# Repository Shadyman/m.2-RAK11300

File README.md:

# RAK11300 LoRa Module on m.2 Key A-E

This is a board in the _m.2 Key A-E_ form factor to allow the use of the [RAK11300](https://docs.rakwireless.com/Product-Categories/WisDuo/RAK11300-Module/) module. 

RAK11300 contains an RP2040 microcontroller, an SX1262 and supporting circuitry on a castellated green PCB. The RAK11300 provides 8xx-9xxMhz-Band communications, depending on the model used. The RAK11300L variant may be substituted, and operates on 433 or 470 Mhz depending on the model.

# m.2 Pins Used
- PERST0n
- Vendor-Defined 38,40,42
- W_DISABLEn
- LED_1n
- LED_2n
- USB+/-

# RAK11300 Pins Used
- RESETn
- BOOT
- SWCLK/SWDIO
- GPIO6, 9, 22, 23, 24
- USB_DP/_DM

# Project Status
- [x] Schematic Creation
- [ ] PCB Creation
  - [X] PCB Layout
  - [ ] TODO: Verify BOOT/SWCLK/SWDIO pinout vs other modules for ease of use
  - [ ] TODO: Calculate LED series resistors where needed
- [ ] Initial PCB Test Run
  - [ ] Finalize BOM
  - [ ] Assembly
- [ ] PCB Testing

# References
- [RAK11300 Item Page - RAK Store](https://store.rakwireless.com/products/wisduo-lpwan-module-rak11300)
- [RAK11300 WisDuo LPWAN Module - Reference Documents](https://docs.rakwireless.com/Product-Categories/WisDuo/RAK11300-Module/Overview/)
  - Backup snapshot of reference documents and .STL file available in /Documents/
- [SX1262 Product Page - Semtech](https://www.semtech.com/products/wireless-rf/lora-connect/sx1262)

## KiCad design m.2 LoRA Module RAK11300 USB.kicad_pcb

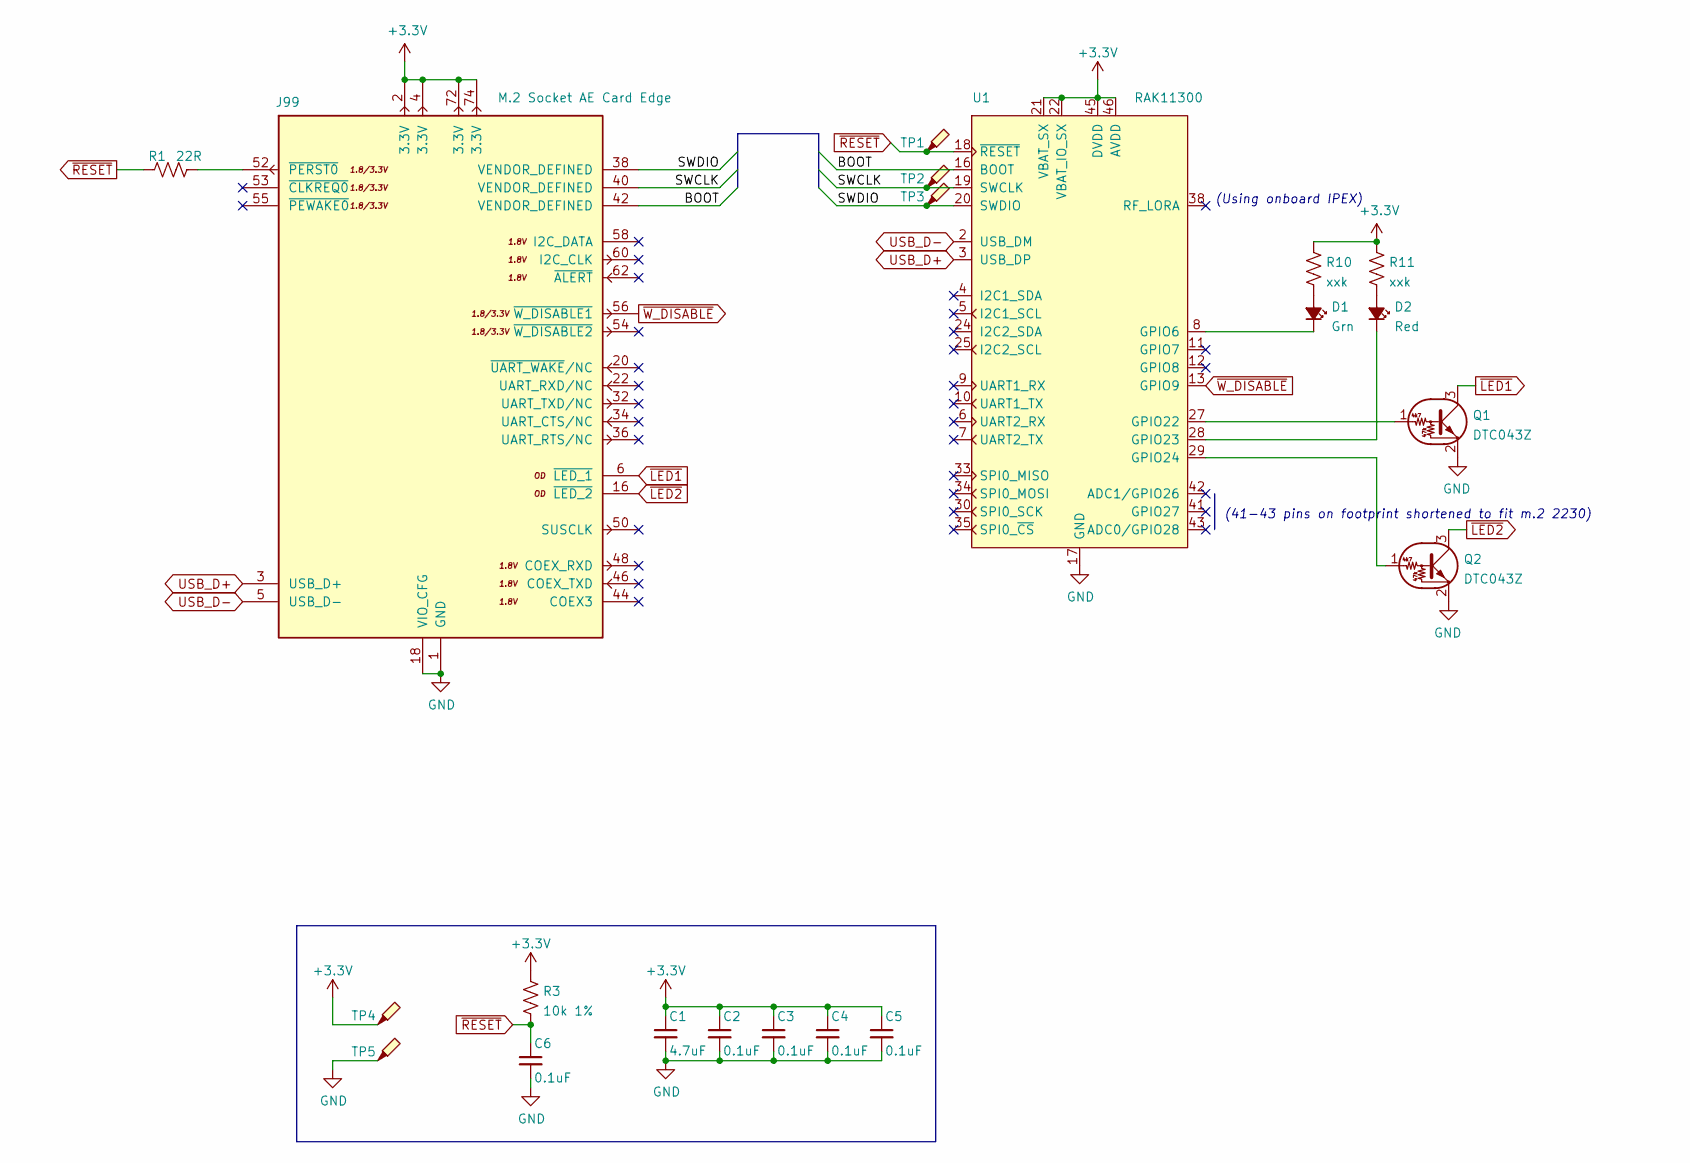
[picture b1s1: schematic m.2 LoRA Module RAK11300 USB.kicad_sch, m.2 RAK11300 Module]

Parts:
C1: 4.7uF; C_0603_1608Metric
C2, C3, C4, C5, C6: 0.1uF; C_0402_1005Metric
D1: Grn; LED_0603_1608Metric; MPN 19-217-R6C-AL1M2VY-3T
D2: Red; LED_0603_1608Metric; MPN 19-217-G7C-AN1P2-3T
J99: M.2 Socket AE Card Edge; m2-padKeyAE
Q1, Q2: DTC043Z; SOT-416; MPN DTC043ZEBTL
R1: 22R; R_0402_1005Metric
R3: 10k 1%; R_0402_1005Metric
R10, R11: xxk; R_0402_1005Metric
TP1, TP2, TP3, TP4, TP5: TestPoint_Probe; TestPoint_Pad_D1.5mm
U1: RAK11300

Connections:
+3V3: C1.1, C2.1, C3.1, C4.1, C5.1, J99.2 (3.3V), J99.4 (3.3V), J99.72 (3.3V), J99.74 (3.3V), R3.1, R10.1, R11.1, TP4.1, U1.21 (VBAT_SX), U1.22 (VBAT_IO_SX), U1.45 (DVDD), U1.46 (AVDD)
/BOOT: J99.42 (VENDOR_DEFINED), U1.16 (BOOT)
/I2C1_SCL: U1.5 (I2C1_SCL)
/I2C1_SDA: U1.4 (I2C1_SDA)
/SWCLK: J99.40 (VENDOR_DEFINED), TP2.1, U1.19 (SWCLK)
/SWDIO: J99.38 (VENDOR_DEFINED), TP3.1, U1.20 (SWDIO)
GND: C1.2, C2.2, C3.2, C4.2, C5.2, C6.2, J99.1 (GND), J99.7 (GND), J99.18 (VIO_CFG), J99.33 (GND), J99.39 (GND), J99.45 (GND), J99.51 (GND), J99.57 (GND), J99.63 (GND), J99.69 (GND), J99.75 (GND), Q1.2 (E), Q2.2 (E), TP5.1, U1.14 (GND), U1.17 (GND), U1.23 (GND), U1.36 (GND), U1.37 (GND), U1.40 (GND), U1.44 (GND)
unnamed: D1.1 (K), U1.8 (GPIO6)
unnamed: D1.2 (A), R10.2
unnamed: D2.1 (K), U1.28 (GPIO23)
unnamed: D2.2 (A), R11.2
unnamed: J99.52 (~PERST0), R1.1
unnamed: Q1.1 (B), U1.27 (GPIO22)
unnamed: Q2.1 (B), U1.29 (GPIO24)
USB_D+: J99.3 (USB_D+), U1.3 (USB_DP)
USB_D-: J99.5 (USB_D-), U1.2 (USB_DM)
~LED1: J99.6 (~LED_1), Q1.3 (C)
~LED2: J99.16 (~LED_2), Q2.3 (C)
~RESET: C6.1, R1.2, R3.2, TP1.1, U1.18 (~RESET)
~W_DISABLE: J99.56 (~W_DISABLE1), U1.13 (GPIO9)

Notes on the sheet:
(Using onboard IPEX)
(41-43 pins on footprint shortened to fit m.2 2230)

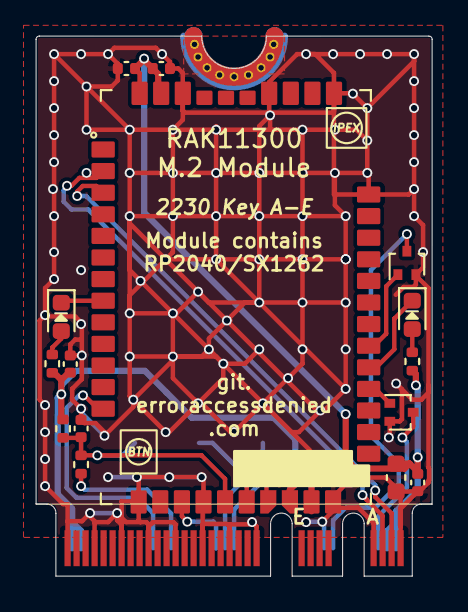
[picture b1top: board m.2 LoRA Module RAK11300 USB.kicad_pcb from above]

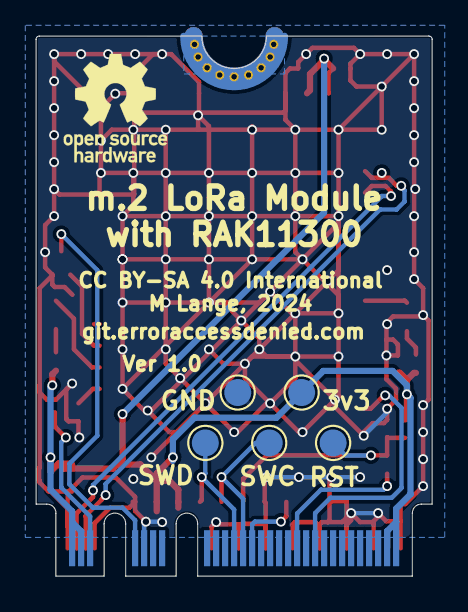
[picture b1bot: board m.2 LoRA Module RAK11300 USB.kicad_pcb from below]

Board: 2 copper layers, 22.0 x 30.0 mm, 22 parts (5 on the bottom side), 18 nets.

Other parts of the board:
J98: m.2-ngff-outline-copper

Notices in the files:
m.2 LoRA Module RAK11300 USB.kicad_pcb:
CC BY-SA 4.0 International
